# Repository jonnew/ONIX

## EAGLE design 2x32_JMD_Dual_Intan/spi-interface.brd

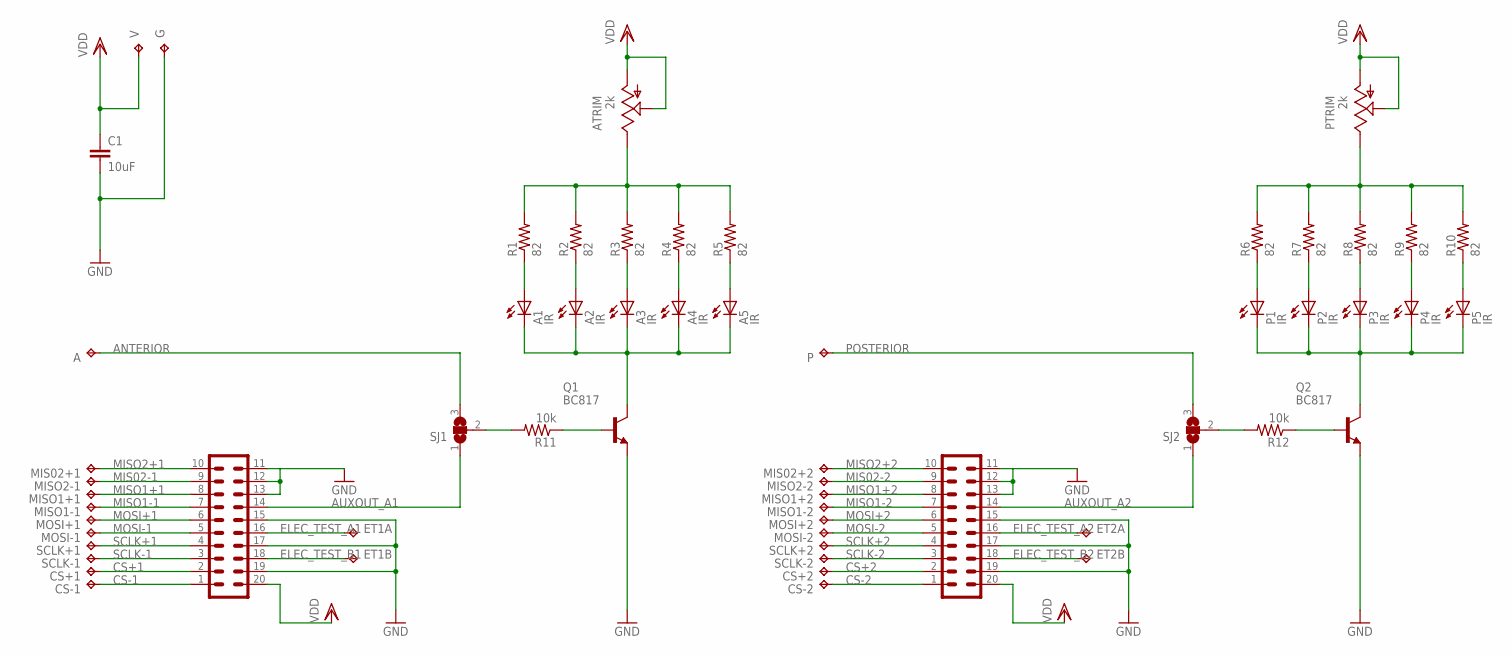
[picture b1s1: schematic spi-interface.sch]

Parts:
A: TP_01; TP01
A1, A2, A3, A4, A5: IR; LED-0603
ATRIM: 2k; EIA/EIAJ
C1: 10uF; 0805
CS+1, CS+2: TP_01; TP01
CS-1, CS-2: TP_01; TP01
ET1A, ET1B, ET2A, ET2B: TP_03; TP03
G: TP_02; TP02
HS1, HS2: JMD20-V
MIS02+1, MIS02+2: TP_01; TP01
MISO1+1, MISO1+2, MISO1-1, MISO1-2, MISO2-1, MISO2-2: TP_01; TP01
MOSI+1, MOSI+2: TP_01; TP01
MOSI-1, MOSI-2: TP_01; TP01
P: TP_01; TP01
P1, P2, P3, P4, P5: IR; LED-0603
PTRIM: 2k; EIA/EIAJ
Q1, Q2: BC817; SOT23-BEC
R1, R2, R3, R4, R5, R6, R7, R8, R9, R10: 82; 0402
R11, R12: 10k; 0402
SCLK+1, SCLK+2: TP_01; TP01
SCLK-1, SCLK-2: TP_01; TP01
SJ1, SJ2: SJ2W; SJ_2
V: TP_02; TP02

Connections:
ANTERIOR: A.TP, SJ1.3
AUXOUT_A1: HS1.14, SJ1.1
AUXOUT_A2: HS2.14, SJ2.1
B2: P1.C, P2.C, P3.C, P4.C, P5.C, Q2.C
CS+1: CS+1.TP, HS1.2
CS+2: CS+2.TP, HS2.2
CS-1: CS-1.TP, HS1.1
CS-2: CS-2.TP, HS2.1
ELEC_TEST_A1: ET1A.TP, HS1.16
ELEC_TEST_A2: ET2A.TP, HS2.16
ELEC_TEST_B1: ET1B.TP, HS1.18
ELEC_TEST_B2: ET2B.TP, HS2.18
F1: A1.C, A2.C, A3.C, A4.C, A5.C, Q1.C
GND: C1.2, G.TP, HS1.11, HS1.12, HS1.13, HS1.15, HS1.17, HS1.19, HS2.11, HS2.12, HS2.13, HS2.15, HS2.17, HS2.19, Q1.E, Q2.E
MIS02-1: HS1.9, MISO2-1.TP
MIS02-2: HS2.9, MISO2-2.TP
MISO1+1: HS1.8, MISO1+1.TP
MISO1+2: HS2.8, MISO1+2.TP
MISO1-1: HS1.7, MISO1-1.TP
MISO1-2: HS2.7, MISO1-2.TP
MISO2+1: HS1.10, MIS02+1.TP
MISO2+2: HS2.10, MIS02+2.TP
MOSI+1: HS1.6, MOSI+1.TP
MOSI+2: HS2.6, MOSI+2.TP
MOSI-1: HS1.5, MOSI-1.TP
MOSI-2: HS2.5, MOSI-2.TP
unnamed: ATRIM.E, R1.2, R2.2, R3.2, R4.2, R5.2
unnamed: P1.A, R6.1
unnamed: A1.A, R1.1
unnamed: R12.2, SJ2.2
unnamed: Q2.B, R12.1
unnamed: PTRIM.E, R6.2, R7.2, R8.2, R9.2, R10.2
unnamed: A2.A, R2.1
unnamed: A3.A, R3.1
unnamed: A4.A, R4.1
unnamed: A5.A, R5.1
unnamed: P2.A, R7.1
unnamed: P3.A, R8.1
unnamed: P4.A, R9.1
unnamed: P5.A, R10.1
unnamed: Q1.B, R11.1
unnamed: R11.2, SJ1.2
POSTERIOR: P.TP, SJ2.3
SCLK+1: HS1.4, SCLK+1.TP
SCLK+2: HS2.4, SCLK+2.TP
SCLK-1: HS1.3, SCLK-1.TP
SCLK-2: HS2.3, SCLK-2.TP
VDD: ATRIM.A, ATRIM.S, C1.1, HS1.20, HS2.20, PTRIM.A, PTRIM.S, V.TP

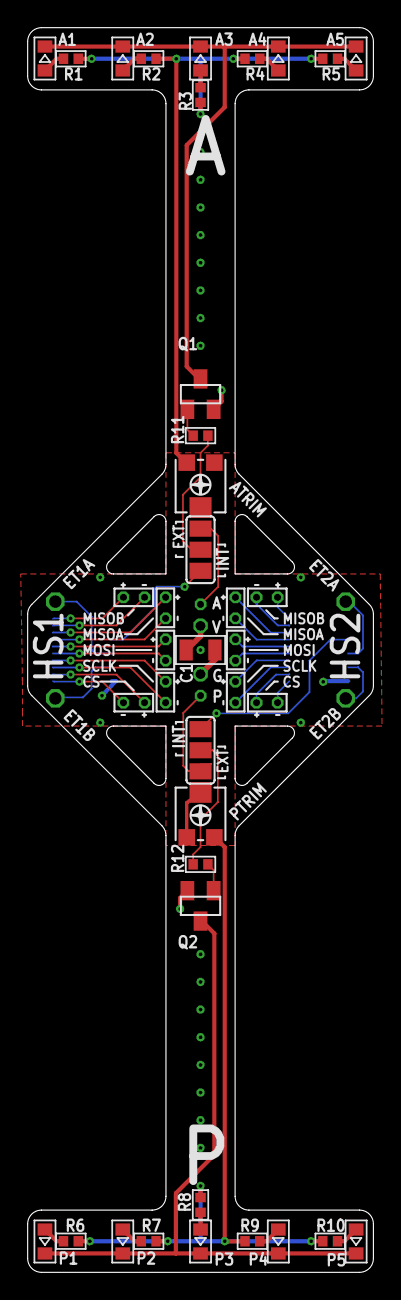
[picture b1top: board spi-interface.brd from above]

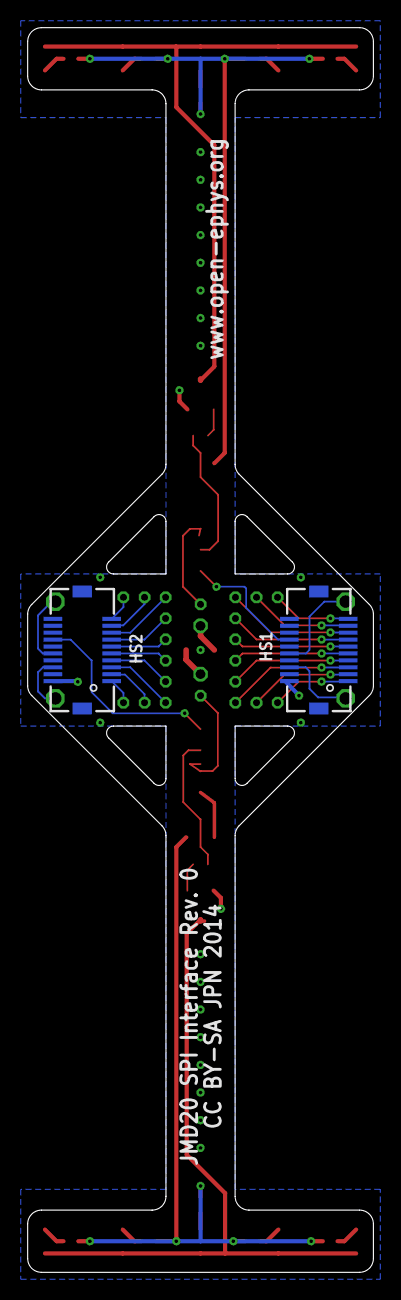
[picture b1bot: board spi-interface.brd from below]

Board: 4 copper layers, 25.0 x 90.0 mm, 59 parts (2 on the bottom side), 48 nets.

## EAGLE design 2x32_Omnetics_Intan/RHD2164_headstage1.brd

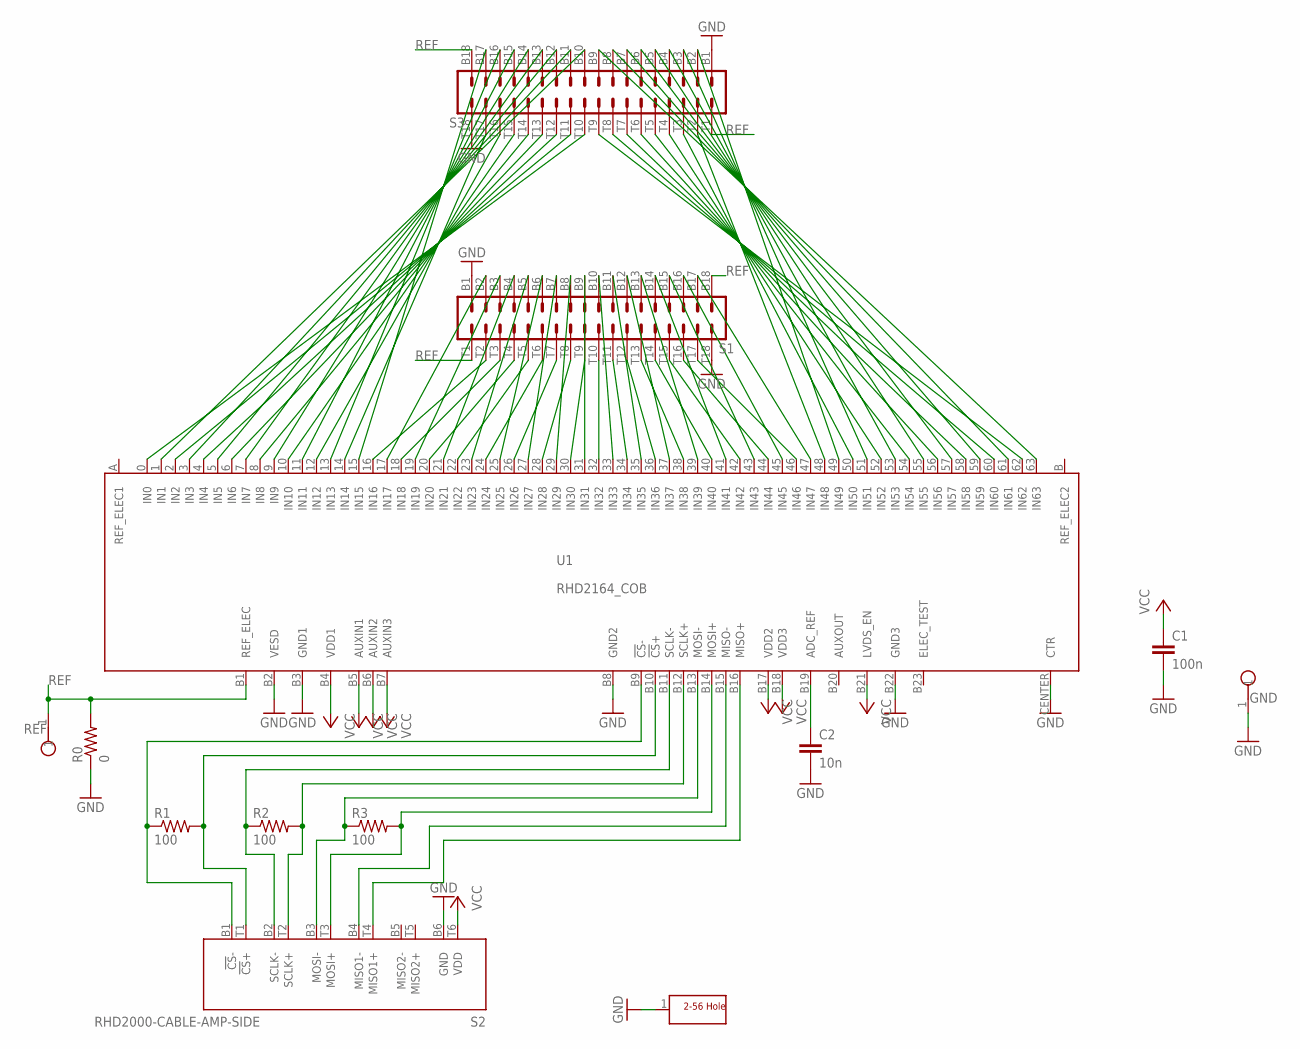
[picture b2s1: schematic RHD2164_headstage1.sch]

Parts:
C1: 100n; 0402
C2: 10n; 0201
GND: TESTPOINT_SMALL
H1: SCREW_HOLE_2-56
R0: 0; 0402
R1, R2, R3: 100; 0201
REF: TESTPOINT_SMALL
S1, S3: OMNETICS_A79025
S2: RHD2000-CABLE-AMP-SIDE; OMNETICS_PZN-12-AA
U1: RHD2164_COB

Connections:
GND: C1.2, C2.2, GND.1, H1.1, R0.1, S1.B1, S1.T18, S2.B6 (GND), S3.B1, S3.T18, U1.B2 (VESD), U1.B3 (GND1), U1.B8 (GND2), U1.B22 (GND3), U1.CENTER (CTR)
unnamed: S2.T4 (MISO1+), U1.B16 (MISO+)
unnamed: S1.T2, U1.16 (IN16)
unnamed: S1.B2, U1.17 (IN17)
unnamed: S1.T3, U1.18 (IN18)
unnamed: S1.B3, U1.19 (IN19)
unnamed: S1.T4, U1.20 (IN20)
unnamed: S1.B4, U1.21 (IN21)
unnamed: S1.T5, U1.22 (IN22)
unnamed: S1.B5, U1.23 (IN23)
unnamed: S1.T6, U1.24 (IN24)
unnamed: R1.1, S2.B1 (!CS!-), U1.B9 (!CS!-)
unnamed: S1.B6, U1.25 (IN25)
unnamed: S1.T7, U1.26 (IN26)
unnamed: S1.B7, U1.27 (IN27)
unnamed: S1.T8, U1.28 (IN28)
unnamed: S1.B8, U1.29 (IN29)
unnamed: S1.T9, U1.30 (IN30)
unnamed: S1.B9, U1.31 (IN31)
unnamed: S1.T10, U1.32 (IN32)
unnamed: S1.B10, U1.33 (IN33)
unnamed: S1.T11, U1.34 (IN34)
unnamed: S1.B11, U1.35 (IN35)
unnamed: S1.T12, U1.36 (IN36)
unnamed: S1.B12, U1.37 (IN37)
unnamed: S1.T13, U1.38 (IN38)
unnamed: S1.B13, U1.39 (IN39)
unnamed: S1.T14, U1.40 (IN40)
unnamed: S1.B14, U1.41 (IN41)
unnamed: S1.T15, U1.42 (IN42)
unnamed: S1.B15, U1.43 (IN43)
unnamed: S1.T16, U1.44 (IN44)
unnamed: S1.B16, U1.45 (IN45)
unnamed: S1.T17, U1.46 (IN46)
unnamed: S1.B17, U1.47 (IN47)
unnamed: R1.2, S2.T1 (!CS!+), U1.B10 (!CS!+)
unnamed: R2.1, S2.B2 (SCLK-), U1.B11 (SCLK-)
unnamed: R2.2, S2.T2 (SCLK+), U1.B12 (SCLK+)
unnamed: R3.1, S2.B3 (MOSI-), U1.B13 (MOSI-)
unnamed: R3.2, S2.T3 (MOSI+), U1.B14 (MOSI+)
unnamed: S2.B4 (MISO1-), U1.B15 (MISO-)
unnamed: S3.B17, U1.15 (IN15)
unnamed: C2.1, U1.B19 (ADC_REF)
unnamed: S3.T17, U1.14 (IN14)
unnamed: S3.B16, U1.13 (IN13)
unnamed: S3.T16, U1.12 (IN12)
unnamed: S3.B15, U1.11 (IN11)
unnamed: S3.T15, U1.10 (IN10)
unnamed: S3.B14, U1.9 (IN9)
unnamed: S3.T14, U1.8 (IN8)
unnamed: S3.B13, U1.7 (IN7)
unnamed: S3.T13, U1.6 (IN6)
unnamed: S3.B12, U1.5 (IN5)
unnamed: S3.T12, U1.4 (IN4)
unnamed: S3.B11, U1.3 (IN3)
unnamed: S3.T11, U1.2 (IN2)
unnamed: S3.B10, U1.1 (IN1)
unnamed: S3.T10, U1.0 (IN0)
unnamed: S3.T2, U1.48 (IN48)
unnamed: S3.B2, U1.49 (IN49)
unnamed: S3.T3, U1.50 (IN50)
unnamed: S3.B3, U1.51 (IN51)
unnamed: S3.T4, U1.52 (IN52)
unnamed: S3.B4, U1.53 (IN53)
unnamed: S3.T5, U1.54 (IN54)
unnamed: S3.B5, U1.55 (IN55)
unnamed: S3.T6, U1.56 (IN56)
unnamed: S3.B6, U1.57 (IN57)
unnamed: S3.T7, U1.58 (IN58)
unnamed: S3.B7, U1.59 (IN59)
unnamed: S3.T8, U1.60 (IN60)
unnamed: S3.B8, U1.61 (IN61)
unnamed: S3.T9, U1.62 (IN62)
unnamed: S3.B9, U1.63 (IN63)
REF: R0.2, REF.1, S1.B18, S1.T1, S3.B18, S3.T1, U1.B1 (REF_ELEC)
VCC: C1.1, S2.T6 (VDD), U1.B4 (VDD1), U1.B5 (AUXIN1), U1.B6 (AUXIN2), U1.B7 (AUXIN3), U1.B17 (VDD2), U1.B18 (VDD3), U1.B21 (LVDS_EN)

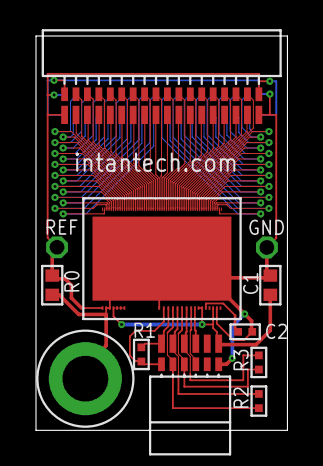
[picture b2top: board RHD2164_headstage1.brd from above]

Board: 2 copper layers, 14.0 x 21.9 mm, 13 parts (1 on the bottom side), 76 nets.

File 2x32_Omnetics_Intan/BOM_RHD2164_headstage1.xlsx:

Bill of Materials |  | RHD2164 Headstage 1 Board |  | Intan Technologies, LLC
Part | Value | Device | Package | Digi-Key part number | Notes
C1 | 100 nF (0.1 uF) | ceramic capacitor (25 V) | 0402 | 445-4964-1-ND
C2 | 10 nF (10000 pF) | ceramic capacitor (16 V) | 0201 | 311-1404-1-ND
R0 | 0 | resistor | 0402 | P0.0JCT-ND
R1 | 100 | resistor | 0201 | P100AGCT-ND
R2 | 100 | resistor | 0201 | P100AGCT-ND
R3 | 100 | resistor | 0201 | P100AGCT-ND
S1 | NSD-36-AA-GS | nano strip connector | 36-pin, 4 guides | Omnetics A79025-001
S2 | PZN-12-AA | polarized nano connector | polarized 12-pin | Omnetics A79623-001
S3 | NSD-36-AA-GS | nano strip connector | 36-pin, 4 guides | Omnetics A79025-001
U1 | RHD2164 | 32-channel amplifier chip | QFN-56L | Intan RHD2164

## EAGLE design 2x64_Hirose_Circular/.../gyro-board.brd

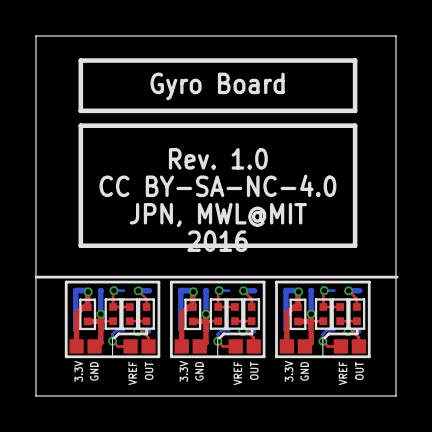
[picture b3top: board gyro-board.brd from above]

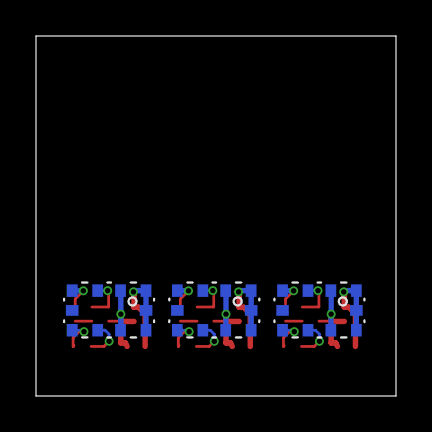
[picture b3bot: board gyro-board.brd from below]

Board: 4 copper layers, 20.0 x 20.0 mm, 27 parts (3 on the bottom side), 14 nets.

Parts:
C1, C2, C5, C6, C8, C9: 470nF; 0201
C3, C4, C7: 10nF; 0201
R1, R2, R3: 10k; 0201
TP1, TP2, TP3, TP4, TP5, TP6, TP7, TP8, TP9, TP10, TP11, TP12: TP08SQ
U1, U2, U3: LY3200; LGA-10-COMPACT

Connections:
+3.3V: C1.1, C6.1, C9.1, TP1.TP, TP4.TP, TP9.TP, U1.1, U1.9, U1.10, U2.1, U2.9, U2.10, U3.1, U3.9, U3.10
GND: C1.2, C3.2, C4.2, C6.2, C7.2, C9.2, R1.2, R2.2, R3.2, TP3.TP, TP7.TP, TP11.TP, U1.2, U1.4, U1.8, U2.2, U2.4, U2.8, U3.2, U3.4, U3.8
unnamed: C4.1, C5.1, U2.3
unnamed: C5.2, R2.1
unnamed: C2.1, C3.1, U1.3
unnamed: C2.2, R1.1
unnamed: C7.1, C8.1, U3.3
unnamed: C8.2, R3.1
OUT: TP2.TP, U1.6
OUT1: TP6.TP, U2.6
OUT2: TP10.TP, U3.6
VREF: TP5.TP, U1.7
VREF1: TP8.TP, U2.7
VREF2: TP12.TP, U3.7

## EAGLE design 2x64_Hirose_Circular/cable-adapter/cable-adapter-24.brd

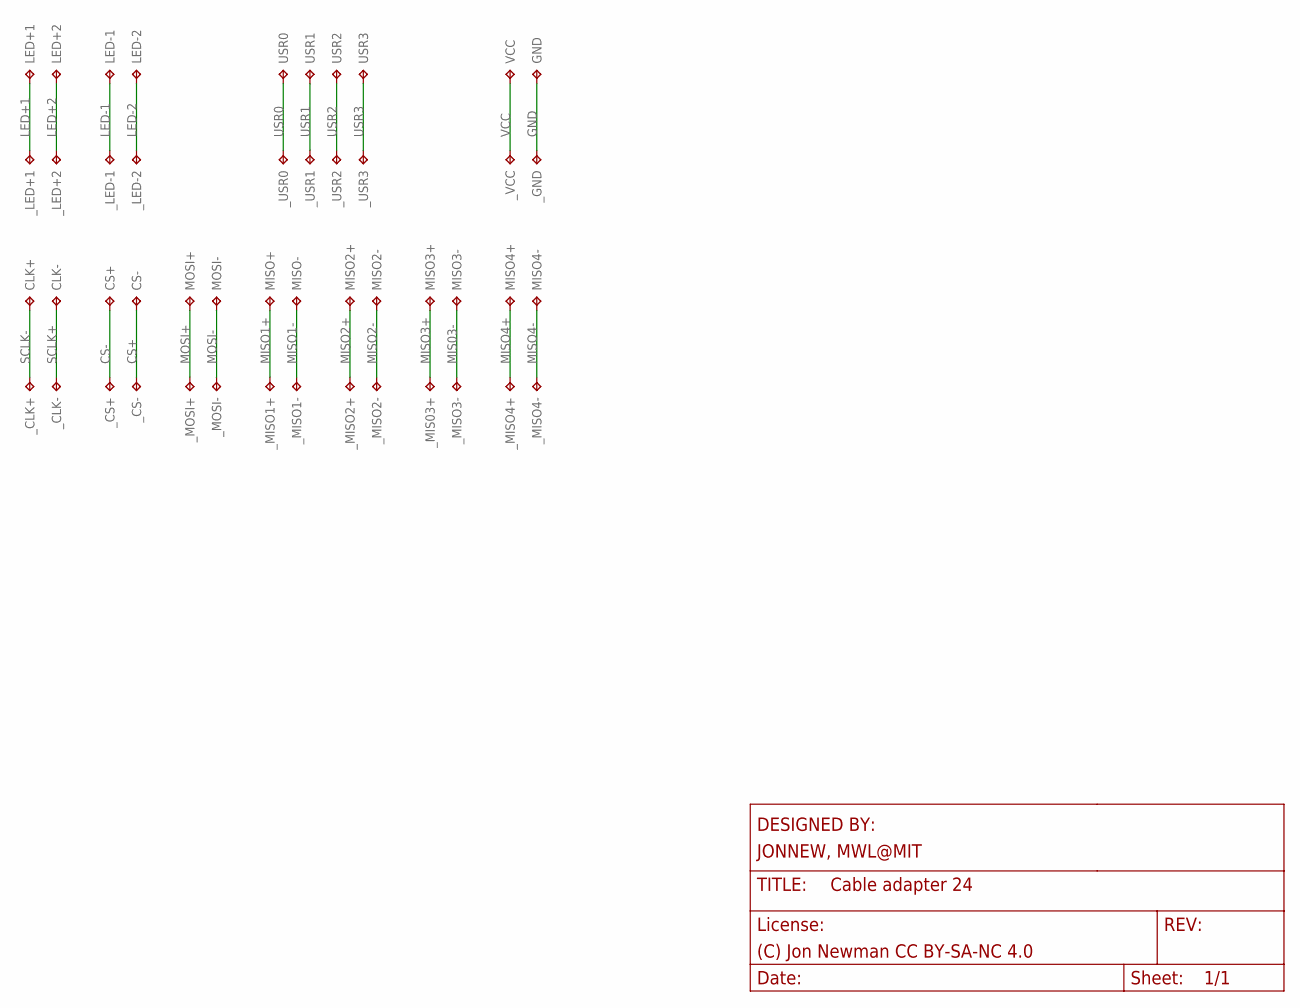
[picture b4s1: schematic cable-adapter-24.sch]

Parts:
CLK+: TP_SPI_WIRE+; SPI_WIRE+
CLK-: TP_SPI_WIRE+; SPI_WIRE+
CS+: TP_SPI_WIRE+; SPI_WIRE+
CS-: TP_SPI_WIRE+; SPI_WIRE+
GND: TP_SPI_WIRE+; SPI_WIRE+
LED+1, LED+2: TP_SPI_WIRE+; SPI_WIRE+
LED-1, LED-2: TP_SPI_WIRE+; SPI_WIRE+
MISO2+, MISO2-, MISO3+, MISO3-, MISO4+, MISO4-: TP_SPI_WIRE+; SPI_WIRE+
MISO+: TP_SPI_WIRE+; SPI_WIRE+
MISO-: TP_SPI_WIRE+; SPI_WIRE+
MOSI+: TP_SPI_WIRE+; SPI_WIRE+
MOSI-: TP_SPI_WIRE+; SPI_WIRE+
USR0, USR1, USR2, USR3: TP_SPI_WIRE+; SPI_WIRE+
VCC: TP_SPI_WIRE+; SPI_WIRE+
_CLK+: TP_SPI_WIRE+; SPI_WIRE+
_CLK-: TP_SPI_WIRE+; SPI_WIRE+
_CS+: TP_SPI_WIRE+; SPI_WIRE+
_CS-: TP_SPI_WIRE+; SPI_WIRE+
_GND: TP_SPI_WIRE+; SPI_WIRE+
_LED+1, _LED+2: TP_SPI_WIRE+; SPI_WIRE+
_LED-1, _LED-2: TP_SPI_WIRE+; SPI_WIRE+
_MIS03+: TP_SPI_WIRE+; SPI_WIRE+
_MISO1+, _MISO1-, _MISO2+, _MISO2-, _MISO4+, _MISO4-: TP_SPI_WIRE+; SPI_WIRE+
_MISO3-: MISO3+; SPI_WIRE+
_MOSI+: TP_SPI_WIRE+; SPI_WIRE+
_MOSI-: TP_SPI_WIRE+; SPI_WIRE+
_USR0, _USR1, _USR2, _USR3: TP_SPI_WIRE+; SPI_WIRE+
_VCC: TP_SPI_WIRE+; SPI_WIRE+

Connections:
CS+: CS-.P$1, _CS-.P$1
CS-: CS+.P$1, _CS+.P$1
GND: GND.P$1, _GND.P$1
LED+1: LED+1.P$1, _LED+1.P$1
LED+2: LED+2.P$1, _LED+2.P$1
LED-1: LED-1.P$1, _LED-1.P$1
LED-2: LED-2.P$1, _LED-2.P$1
MIS03-: MISO3-.P$1, _MISO3-.P$1
MISO1+: MISO+.P$1, _MISO1+.P$1
MISO1-: MISO-.P$1, _MISO1-.P$1
MISO2+: MISO2+.P$1, _MISO2+.P$1
MISO2-: MISO2-.P$1, _MISO2-.P$1
MISO3+: MISO3+.P$1, _MIS03+.P$1
MISO4+: MISO4+.P$1, _MISO4+.P$1
MISO4-: MISO4-.P$1, _MISO4-.P$1
MOSI+: MOSI+.P$1, _MOSI+.P$1
MOSI-: MOSI-.P$1, _MOSI-.P$1
SCLK+: CLK-.P$1, _CLK-.P$1
SCLK-: CLK+.P$1, _CLK+.P$1
USR0: USR0.P$1, _USR0.P$1
USR1: USR1.P$1, _USR1.P$1
USR2: USR2.P$1, _USR2.P$1
USR3: USR3.P$1, _USR3.P$1
VCC: VCC.P$1, _VCC.P$1

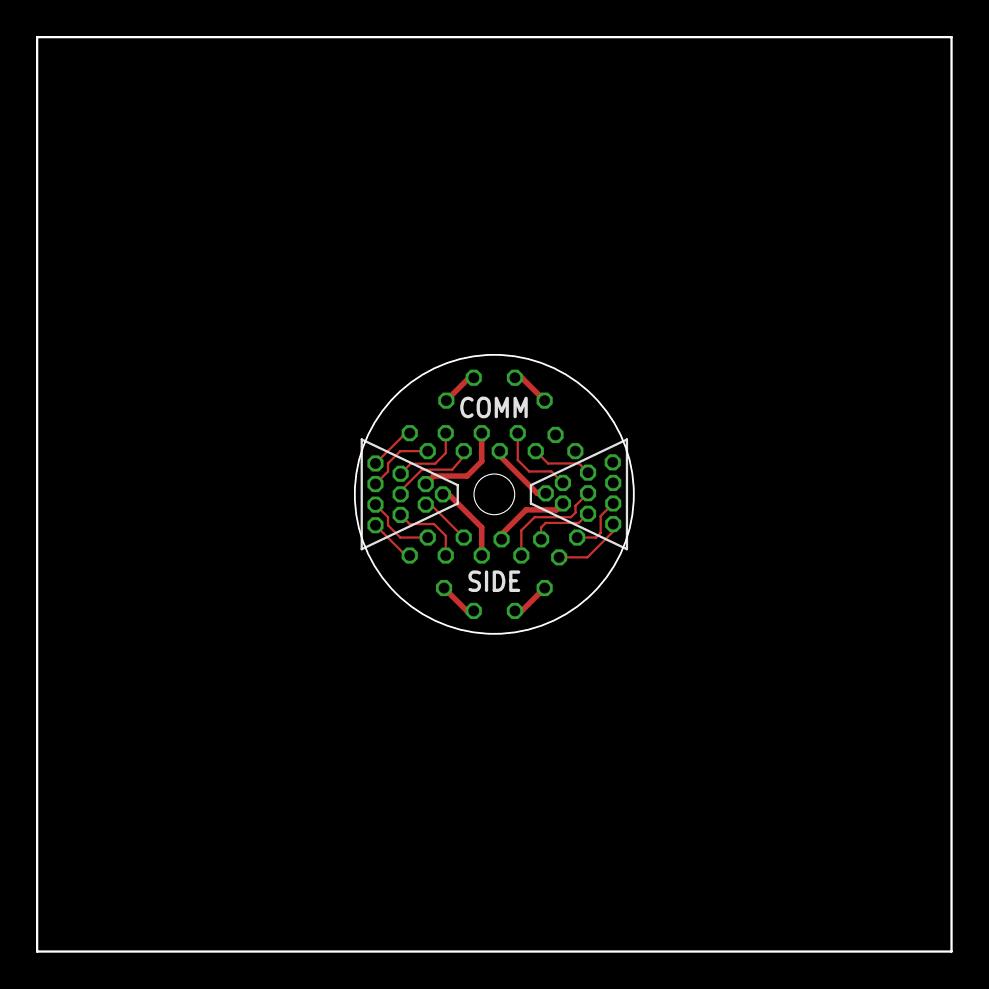
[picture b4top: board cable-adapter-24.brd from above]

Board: 4 copper layers, 50.8 x 50.8 mm, 48 parts (1 on the bottom side), 24 nets.

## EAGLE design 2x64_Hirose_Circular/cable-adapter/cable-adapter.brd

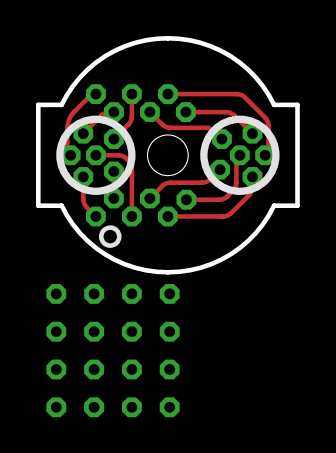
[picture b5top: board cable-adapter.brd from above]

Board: 2 copper layers, 14.4 x 13.0 mm, 40 parts (0 on the bottom side), 18 nets.

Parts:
COM_CLK+: SPI_WIRE+
COM_CLK-: SPI_WIRE+
COM_CS+: SPI_WIRE+
COM_CS-: SPI_WIRE+
COM_GND: SPI_WIRE+
COM_MIS01-, COM_MIS02-, COM_MIS03-, COM_MIS04-: SPI_WIRE+
COM_MISO1+, COM_MISO2+, COM_MISO4+: SPI_WIRE+
COM_MISO3+: MISO3+; SPI_WIRE+
COM_MOSI+: SPI_WIRE+
COM_MOSI-: SPI_WIRE+
COM_RLED1, COM_RLED2: SPI_WIRE+
COM_VCC: SPI_WIRE+
COM_VLED1, COM_VLED2: SPI_WIRE+
T1M_CLK+, T1M_CLK-, T1M_CS+, T1M_CS-, T1M_GND, T1M_MIS01-, T1M_MIS02-\, T1M_MIS03-, T1M_MIS04-, T1M_MISO1+, T1M_MISO2+, T1M_MISO3+, T1M_MISO4+, T1M_MOSI+, T1M_MOSI-, T1M_RLED1, T1M_RLED2, T1M_VCC, T1M_VLED1, T1M_VLED2: SPI_WIRE+

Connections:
+LED: COM_VLED1.P$1, COM_VLED2.P$1, T1M_VLED1.P$1, T1M_VLED2.P$1
-LED: COM_RLED1.P$1, COM_RLED2.P$1, T1M_RLED1.P$1, T1M_RLED2.P$1
CLK+: COM_CLK+.P$1, T1M_CLK+.P$1
CLK-: COM_CLK-.P$1, T1M_CLK-.P$1
CS+: COM_CS+.P$1, T1M_CS+.P$1
CS-: COM_CS-.P$1, T1M_CS-.P$1
GND: COM_GND.P$1, T1M_GND.P$1
MIS02-: COM_MIS02-.P$1, T1M_MIS02-\.P$1
MIS02-1: COM_MIS04-.P$1, T1M_MIS04-.P$1
MISO1+: COM_MISO1+.P$1, T1M_MISO1+.P$1
MISO1+1: COM_MISO3+.P$1, T1M_MISO3+.P$1
MISO1-: COM_MIS01-.P$1, T1M_MIS01-.P$1
MISO1-1: COM_MIS03-.P$1, T1M_MIS03-.P$1
MISO2+: COM_MISO2+.P$1, T1M_MISO2+.P$1
MISO2+1: COM_MISO4+.P$1, T1M_MISO4+.P$1
MOSI+: COM_MOSI+.P$1, T1M_MOSI+.P$1
MOSI-: COM_MOSI-.P$1, T1M_MOSI-.P$1
VCC: COM_VCC.P$1, T1M_VCC.P$1

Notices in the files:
2x32_JMD_Dual_Intan/spi-interface.brd:
CC BY-SA JPN 2014
2x64_Hirose_Circular/.../gyro-board.brd:
CC BY-SA-NC-4.0
2x64_Hirose_Circular/cable-adapter/cable-adapter-24.sch:
LICENSE: (C) Jon Newman CC BY-SA-NC 4.0
